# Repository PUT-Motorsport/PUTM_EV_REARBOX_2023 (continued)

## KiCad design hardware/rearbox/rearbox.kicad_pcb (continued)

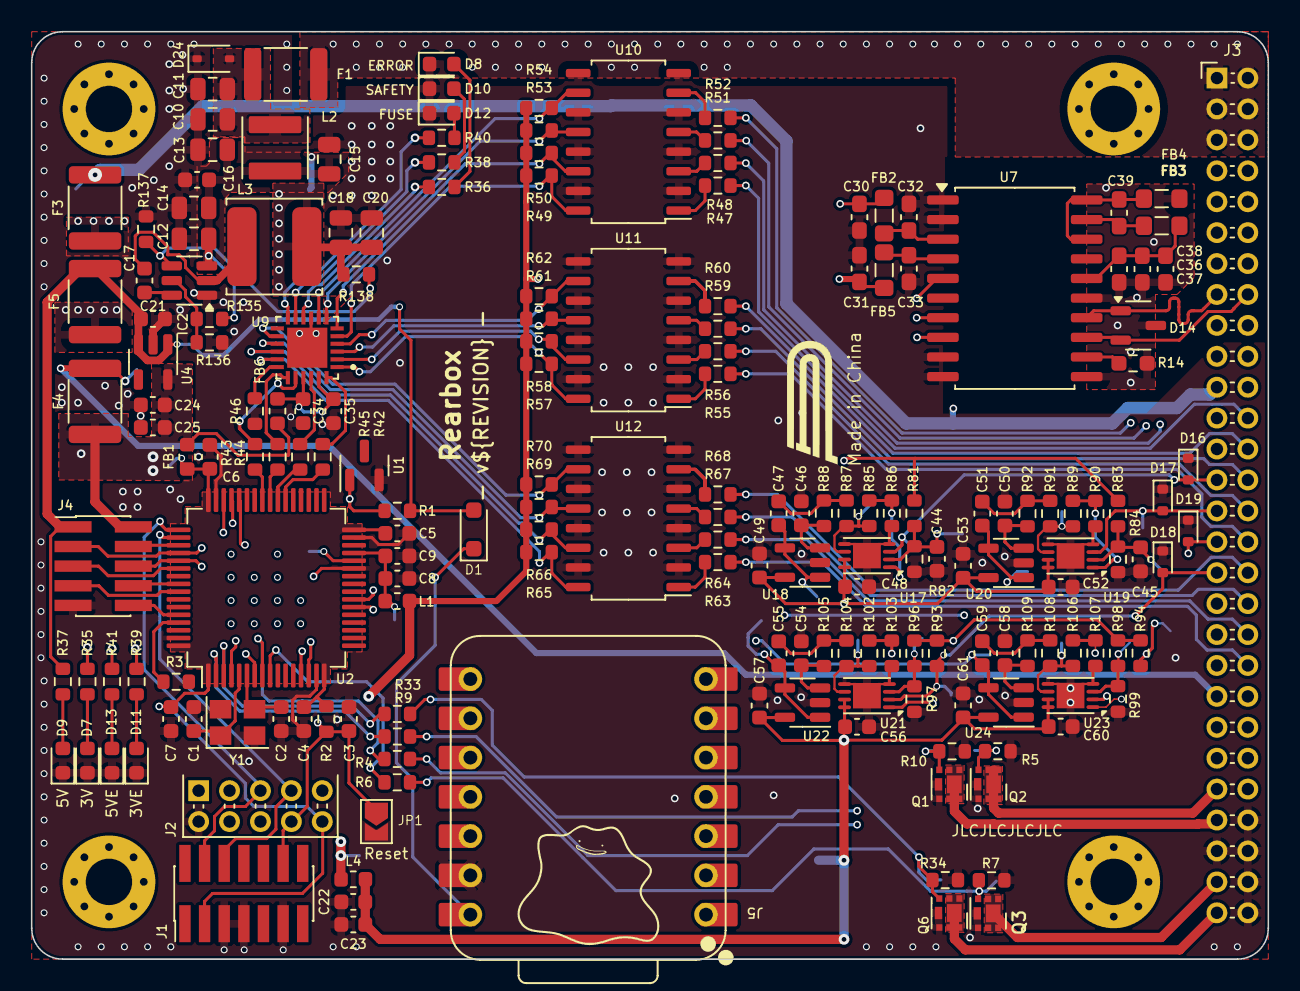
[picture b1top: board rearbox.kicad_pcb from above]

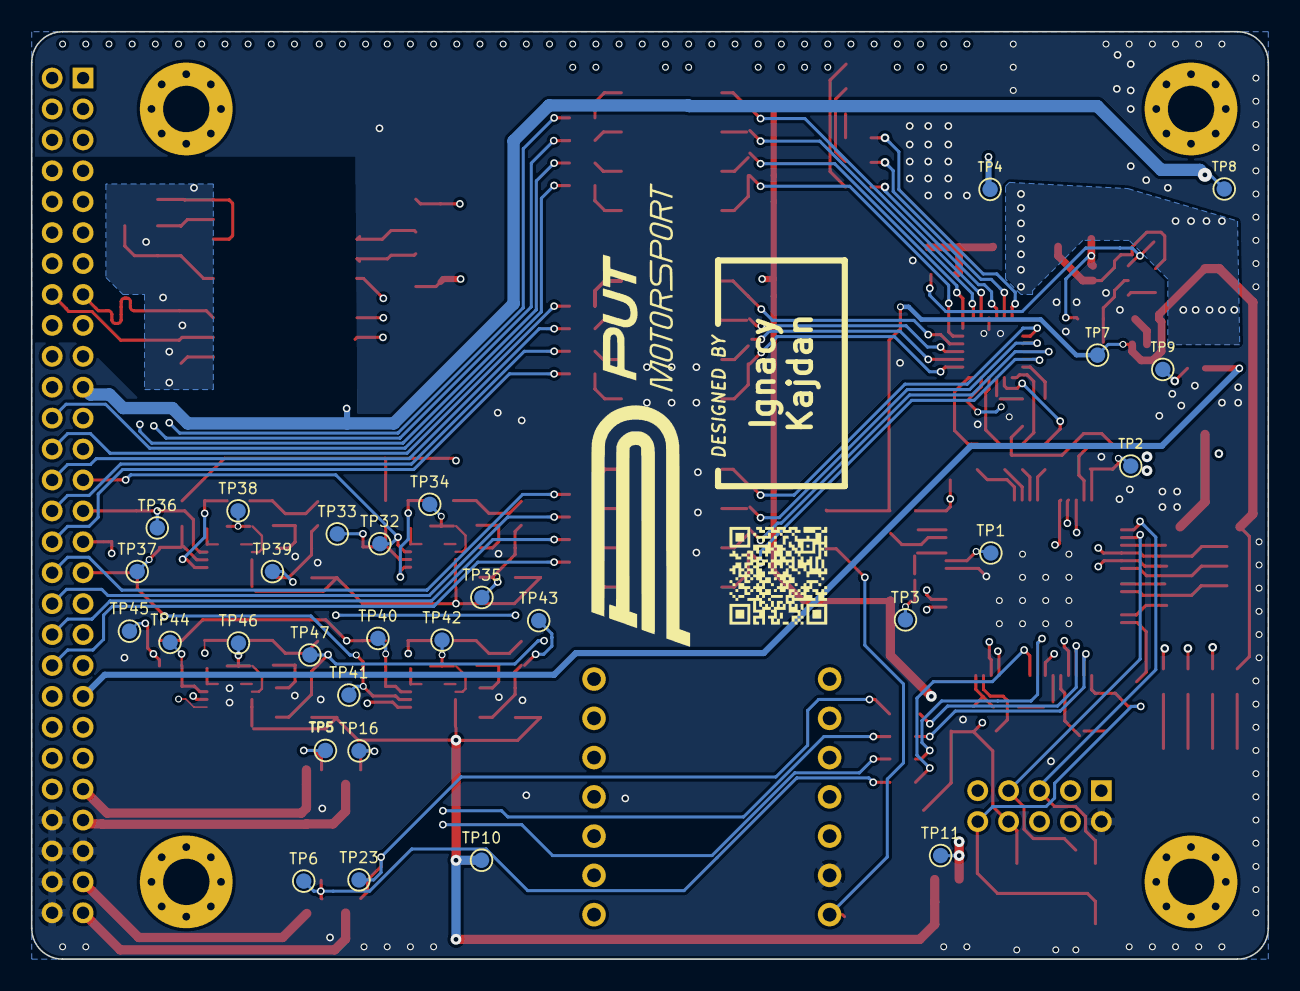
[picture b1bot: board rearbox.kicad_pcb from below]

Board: 4 copper layers, 80.0 x 60.0 mm, 217 parts (29 on the bottom side), 142 nets.

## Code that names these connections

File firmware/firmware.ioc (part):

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Mcu.Name=STM32G473R(B-C-E)Tx
Mcu.Package=LQFP64
Mcu.UserName=STM32G473RCTx
PA1.GPIOParameters=GPIO_Label,GPIO_Mode
PA1.GPIO_Label=WATER_TEMPERATURE1
PA1.GPIO_Mode=GPIO_MODE_ANALOG
PA1.Mode=IN2-Single-Ended
PA1.Signal=ADC1_IN2
PA10.GPIOParameters=GPIO_Label
PA10.GPIO_Label=STBY_CAN
PA10.Signal=GPXTI10
PA11.GPIOParameters=GPIO_Label
PA11.GPIO_Label=CAN_RX
PA11.Mode=FDCAN_Activate
PA11.Signal=FDCAN1_RX
PA12.GPIOParameters=GPIO_Label
PA12.GPIO_Label=CAN_TX
PA12.Mode=FDCAN_Activate
PA12.Signal=FDCAN1_TX
PA13.GPIOParameters=GPIO_Label
PA13.GPIO_Label=SWDIO
PA13.Mode=Serial_Wire
PA13.Signal=SYS_JTMS-SWDIO
PA14.GPIOParameters=GPIO_Label
PA14.GPIO_Label=SWCLK
PA14.Mode=Serial_Wire
PA14.Signal=SYS_JTCK-SWCLK
PA15.GPIOParameters=GPIO_Label
PA15.GPIO_Label=I2C_SCL
PA15.Mode=I2C
PA15.Signal=I2C1_SCL
PA2.GPIOParameters=GPIO_Label
PA2.GPIO_Label=WATER_TEMPERATURE2
PA2.Mode=IN3-Single-Ended
PA2.Signal=ADC1_IN3
PA4.GPIOParameters=GPIO_Label
PA4.GPIO_Label=ANALOG_OFFSET1
PA4.Signal=COMP_DAC11_group
PA5.GPIOParameters=GPIO_Label
PA5.GPIO_Label=ANALOG_OFFSET2
PA5.Signal=COMP_DAC12_group
PB3.GPIOParameters=GPIO_Label
PB3.GPIO_Label=SPI_SCLK
PB3.Mode=Full_Duplex_Master
PB3.Signal=SPI3_SCK
PB4.GPIOParameters=GPIO_Label
PB4.GPIO_Label=SPI_MISO
PB4.Mode=Full_Duplex_Master
PB4.Signal=SPI3_MISO
PB7.GPIOParameters=GPIO_Label
PB7.GPIO_Label=I2C_SDA
PB7.Mode=I2C
PB7.Signal=I2C1_SDA
PB8-BOOT0.GPIOParameters=GPIO_Label
PB8-BOOT0.GPIO_Label=BOOT_SELECT
PB8-BOOT0.Signal=GPIO_Output
PC0.GPIOParameters=GPIO_Label
PC0.GPIO_Label=BRAKE_LIGHT
PC0.Signal=GPIO_Output
PC1.GPIOParameters=GPIO_Label
PC1.GPIO_Label=BACKUP_RTDS
PC1.Signal=GPIO_Output
PC10.GPIOParameters=GPIO_Label
PC10.GPIO_Label=UART_TX
PC10.Mode=Asynchronous
PC10.Signal=USART3_TX
PC11.GPIOParameters=GPIO_Label
PC11.GPIO_Label=UART_RX
PC11.Mode=Asynchronous
PC11.Signal=USART3_RX
PC12.GPIOParameters=GPIO_Label
PC12.GPIO_Label=SPI_MOSI
PC12.Mode=Full_Duplex_Master
PC12.Signal=SPI3_MOSI
PC13.GPIOParameters=GPIO_Label
PC13.GPIO_Label=BACKUP_BRAKE_LIGHT
PC13.Signal=GPIO_Output
PC14-OSC32_IN.GPIOParameters=GPIO_Label
PC14-OSC32_IN.GPIO_Label=RTDS
PC14-OSC32_IN.Signal=GPIO_Output
PC15-OSC32_OUT.GPIOParameters=GPIO_Label
PC15-OSC32_OUT.GPIO_Label=XIAO_GPIO
PC15-OSC32_OUT.Signal=GPIO_Output
PC4.GPIOParameters=GPIO_Label
PC4.GPIO_Label=WATER_PRESSURE2
PC4.Mode=IN5-Single-Ended
PC4.Signal=ADC2_IN5
PC5.GPIOParameters=GPIO_Label
PC5.GPIO_Label=WATER_PRESSURE1
PC5.Mode=IN11-Single-Ended
PC5.Signal=ADC2_IN11
PC6.GPIOParameters=PinState,GPIO_PuPd,GPIO_Label
PC6.GPIO_Label=SAFETY_RESET
PC6.GPIO_PuPd=GPIO_PULLUP
PC6.PinState=GPIO_PIN_SET
PC6.Signal=GPIO_Output
PC7.GPIOParameters=GPIO_PuPd,GPIO_Label,GPIO_ModeDefaultEXTI
PC7.GPIO_Label=SAFETY_INT
PC7.GPIO_ModeDefaultEXTI=GPIO_MODE_IT_FALLING
PC7.GPIO_PuPd=GPIO_PULLUP
PC7.Signal=GPXTI7
PC8.GPIOParameters=GPIO_Label,GPIO_Pu
PC8.GPIO_Label=SAFETY_SCL
PC8.GPIO_Pu=GPIO_PULLUP
PC8.Mode=I2C
PC8.Signal=I2C3_SCL
PC9.GPIOParameters=GPIO_Label,GPIO_Pu
PC9.GPIO_Label=SAFETY_SDA
PC9.GPIO_Pu=GPIO_PULLUP
PC9.Mode=I2C
PC9.Signal=I2C3_SDA
PF0-OSC_IN.GPIOParameters=GPIO_Label
PF0-OSC_IN.GPIO_Label=HSE_IN
PF0-OSC_IN.Mode=HSE-External-Oscillator
PF0-OSC_IN.Signal=RCC_OSC_IN
PF1-OSC_OUT.GPIOParameters=GPIO_Label
PF1-OSC_OUT.GPIO_Label=HSE_OUT
PF1-OSC_OUT.Mode=HSE-External-Oscillator
PF1-OSC_OUT.Signal=RCC_OSC_OUT
RCC.HSE_VALUE=48000000
RCC.SYSCLKFreq_VALUE=160000000
RCC.SYSCLKSource=RCC_SYSCLKSOURCE_PLLCLK
board=custom

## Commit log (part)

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2025-01-11 Update safety pins configuration
2025-03-18 Setup for Vs Code
2025-03-18 Fix CAN communication and RTDS
2025-04-17 Changed power section
2025-04-23 Added ESD protection to power section
2025-04-24 Changed text layout on PCB
2025-08-04 Sync :(
2025-08-23 Changing RTDS logic for FSG2025
2025-10-28 Deleted measurement systems for new iteration
2025-10-28 Positioned new CANBUS components on PCB
2025-10-29 Fixed problematic silkscreen placements
2025-11-04 Moved the CAN IC to a less retarded position
2025-11-04 Oops! all bad ISOGND zones!
2025-11-04 Better routing of 5V_EXT and safety lines made to minimise CAN noise
2025-11-04 Fixed badly thought out CAN GND
2025-11-11 Moved CAN IC to shorten CAN traces length and shortened isognd lengths
2025-11-11 Fixed one small detail that piotrus found
2025-11-13 Added an auxillary transistor for rear brakelights in case they burn up again and fixed some GNDISO_CAN problems
2025-11-13 Removed a leftover fill zone
2025-11-13 Fixed an oopsie with a zone fill
2025-11-18 Added an auxillary RTDS transistor as a backup
2025-12-02 Made ferrites into 0805's
2026-01-03 Fixed bad silkscreen placement
2026-03-06 go to cmake and new can lib
2026-03-06 integration on new can lib
2026-03-06 version do debug
2026-03-06 work version
2026-03-07 integration
2026-06-27 First push
2026-06-27 update gitmodules
2026-06-27 update gitignore
2026-06-27 generated Cmake setup
2026-06-27 work in progress
2026-06-27 build version
